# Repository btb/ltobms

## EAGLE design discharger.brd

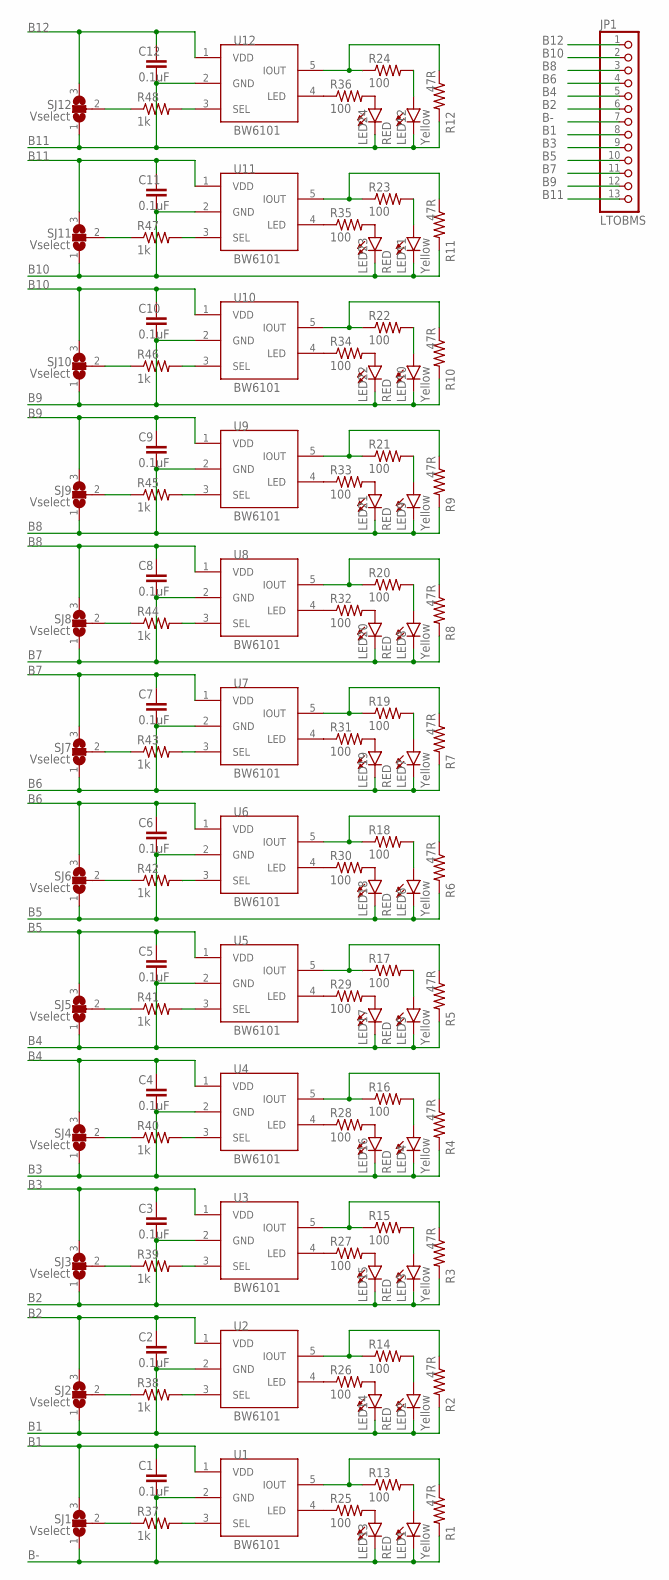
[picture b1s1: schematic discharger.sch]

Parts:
C1, C2, C3, C4, C5, C6, C7, C8, C9, C10, C11, C12: 0.1uF; C0603; LCSCPART# C49678
JP1: LTOBMS; 1X13
LED1, LED2, LED3, LED4, LED5, LED6, LED7, LED8, LED9, LED10, LED11, LED12: Yellow; LED-0603; LCSCPART# C84256
LED13, LED14, LED15, LED16, LED17, LED18, LED19, LED20, LED21, LED22, LED23, LED24: RED; LED-0603; LCSCPART# C84256
R1, R2, R3, R4, R5, R6, R7, R8, R9, R10, R11, R12: 47R; R2512; LCSCPART# C25384
R13, R14, R15, R16, R17, R18, R19, R20, R21, R22, R23, R24, R25, R26, R27, R28, R29, R30, R31, R32, R33, R34, R35, R36: 100; R0603; LCSCPART# C17408
R37, R38, R39, R40, R41, R42, R43, R44, R45, R46, R47, R48: 1k; R0603; LCSCPART# C17513
SJ1, SJ2, SJ3, SJ4, SJ5, SJ6, SJ7, SJ8, SJ9, SJ10, SJ11, SJ12: Vselect; SJ_2
U1, U2, U3, U4, U5, U6, U7, U8, U9, U10, U11, U12: BW6101; SOT23-5L

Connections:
B1: C1.1, C2.2, JP1.8, LED2.C, LED14.C, R2.2, SJ1.3, SJ2.1, U1.1 (VDD), U2.2 (GND)
B2: C2.1, C3.2, JP1.6, LED3.C, LED15.C, R3.2, SJ2.3, SJ3.1, U2.1 (VDD), U3.2 (GND)
B3: C3.1, C4.2, JP1.9, LED4.C, LED16.C, R4.2, SJ3.3, SJ4.1, U3.1 (VDD), U4.2 (GND)
B4: C4.1, C5.2, JP1.5, LED5.C, LED17.C, R5.2, SJ4.3, SJ5.1, U4.1 (VDD), U5.2 (GND)
B5: C5.1, C6.2, JP1.10, LED6.C, LED18.C, R6.2, SJ5.3, SJ6.1, U5.1 (VDD), U6.2 (GND)
B6: C6.1, C7.2, JP1.4, LED7.C, LED19.C, R7.2, SJ6.3, SJ7.1, U6.1 (VDD), U7.2 (GND)
B7: C7.1, C8.2, JP1.11, LED8.C, LED20.C, R8.2, SJ7.3, SJ8.1, U7.1 (VDD), U8.2 (GND)
B8: C8.1, C9.2, JP1.3, LED9.C, LED21.C, R9.2, SJ8.3, SJ9.1, U8.1 (VDD), U9.2 (GND)
B9: C9.1, C10.2, JP1.12, LED10.C, LED22.C, R10.2, SJ9.3, SJ10.1, U9.1 (VDD), U10.2 (GND)
B10: C10.1, C11.2, JP1.2, LED11.C, LED23.C, R11.2, SJ10.3, SJ11.1, U10.1 (VDD), U11.2 (GND)
B11: C11.1, C12.2, JP1.13, LED12.C, LED24.C, R12.2, SJ11.3, SJ12.1, U11.1 (VDD), U12.2 (GND)
B12: C12.1, JP1.1, SJ12.3, U12.1 (VDD)
B-: C1.2, JP1.7, LED1.C, LED13.C, R1.2, SJ1.1, U1.2 (GND)
unnamed: R1.1, R13.1, U1.5 (IOUT)
unnamed: LED1.A, R13.2
unnamed: R25.1, U1.4 (LED)
unnamed: LED2.A, R14.2
unnamed: LED7.A, R19.2
unnamed: R3.1, R15.1, U3.5 (IOUT)
unnamed: R37.1, SJ1.2
unnamed: R38.1, SJ2.2
unnamed: R27.1, U3.4 (LED)
unnamed: LED15.A, R27.2
unnamed: LED8.A, R20.2
unnamed: R39.1, SJ3.2
unnamed: R40.1, SJ4.2
unnamed: LED9.A, R21.2
unnamed: LED13.A, R25.2
unnamed: R8.1, R20.1, U8.5 (IOUT)
unnamed: R41.1, SJ5.2
unnamed: R42.1, SJ6.2
unnamed: R32.1, U8.4 (LED)
unnamed: LED20.A, R32.2
unnamed: R2.1, R14.1, U2.5 (IOUT)
unnamed: R43.1, SJ7.2
unnamed: R44.1, SJ8.2
unnamed: R26.1, U2.4 (LED)
unnamed: LED14.A, R26.2
unnamed: R4.1, R16.1, U4.5 (IOUT)
unnamed: R45.1, SJ9.2
unnamed: R46.1, SJ10.2
unnamed: R28.1, U4.4 (LED)
unnamed: LED16.A, R28.2
unnamed: LED10.A, R22.2
unnamed: LED11.A, R23.2
unnamed: LED12.A, R24.2
unnamed: LED6.A, R18.2
unnamed: LED5.A, R17.2
unnamed: R5.1, R17.1, U5.5 (IOUT)
unnamed: R47.1, SJ11.2
unnamed: R48.1, SJ12.2
unnamed: R29.1, U5.4 (LED)
unnamed: LED17.A, R29.2
unnamed: R9.1, R21.1, U9.5 (IOUT)
unnamed: R48.2, U12.3 (SEL)
unnamed: R47.2, U11.3 (SEL)
unnamed: R33.1, U9.4 (LED)
unnamed: LED21.A, R33.2
unnamed: R6.1, R18.1, U6.5 (IOUT)
unnamed: R46.2, U10.3 (SEL)
unnamed: R45.2, U9.3 (SEL)
unnamed: R30.1, U6.4 (LED)
unnamed: LED18.A, R30.2
unnamed: LED4.A, R16.2
unnamed: LED3.A, R15.2
unnamed: R44.2, U8.3 (SEL)
unnamed: R43.2, U7.3 (SEL)
unnamed: R42.2, U6.3 (SEL)
unnamed: R7.1, R19.1, U7.5 (IOUT)
unnamed: R41.2, U5.3 (SEL)
unnamed: R40.2, U4.3 (SEL)
unnamed: R31.1, U7.4 (LED)
unnamed: LED19.A, R31.2
unnamed: R10.1, R22.1, U10.5 (IOUT)
unnamed: R39.2, U3.3 (SEL)
unnamed: R38.2, U2.3 (SEL)
unnamed: R34.1, U10.4 (LED)
unnamed: LED22.A, R34.2
unnamed: R37.2, U1.3 (SEL)
unnamed: R11.1, R23.1, U11.5 (IOUT)
unnamed: R35.1, U11.4 (LED)
unnamed: LED23.A, R35.2
unnamed: R12.1, R24.1, U12.5 (IOUT)
unnamed: R36.1, U12.4 (LED)
unnamed: LED24.A, R36.2

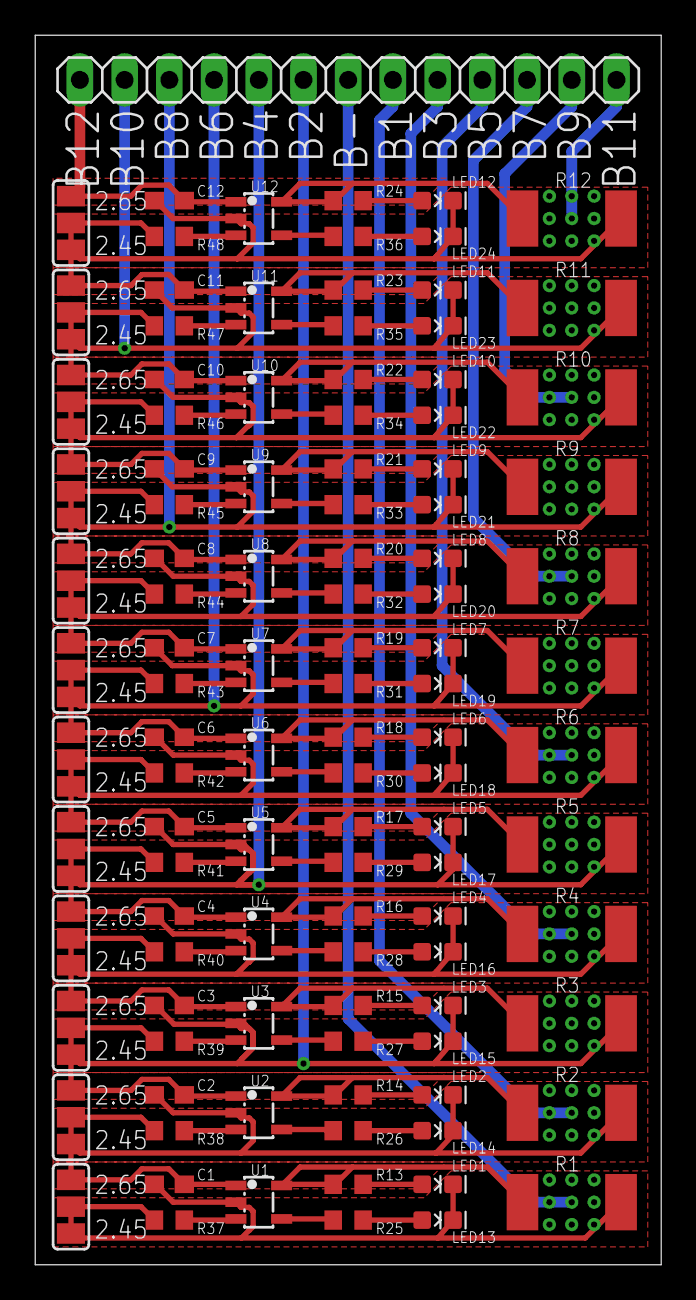
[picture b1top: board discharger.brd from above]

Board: 2 copper layers, 35.6 x 69.8 mm, 109 parts (0 on the bottom side), 85 nets.

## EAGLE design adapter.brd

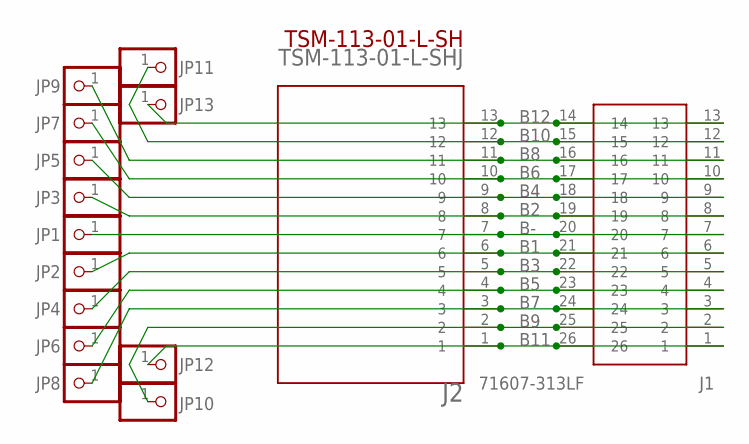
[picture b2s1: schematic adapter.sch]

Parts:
J1: 71607-313LF; 71607313LF
J2: TSM-113-01-L-SHJ; TSM-113-01-L-SH
JP1, JP2, JP3, JP4, JP5, JP6, JP7, JP8, JP9, JP10, JP11, JP12, JP13: PINHD-1X1; 1X01BIG

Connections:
B1: J1.6, J1.21, J2.6, JP2.1
B2: J1.8, J1.19, J2.8, JP3.1
B3: J1.5, J1.22, J2.5, JP4.1
B4: J1.9, J1.18, J2.9, JP5.1
B5: J1.4, J1.23, J2.4, JP6.1
B6: J1.10, J1.17, J2.10, JP7.1
B7: J1.3, J1.24, J2.3, JP8.1
B8: J1.11, J1.16, J2.11, JP9.1
B9: J1.2, J1.25, J2.2, JP10.1
B10: J1.12, J1.15, J2.12, JP11.1
B11: J1.1, J1.26, J2.1, JP12.1
B12: J1.13, J1.14, J2.13, JP13.1
B-: J1.7, J1.20, J2.7, JP1.1

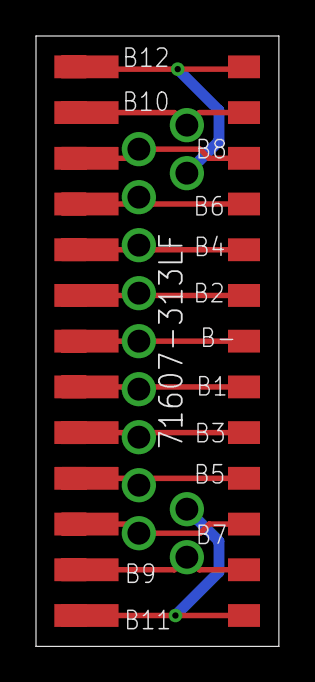
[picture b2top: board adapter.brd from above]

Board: 2 copper layers, 13.5 x 33.9 mm, 15 parts (0 on the bottom side), 13 nets.

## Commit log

2020-08-10 add BMS to SIL adapter board
2020-08-10 add description
2020-08-10 add part library
2020-08-11 add schematic
2020-08-12 make a single cell protector as a design block
2020-08-12 don't use pwr for the BW6101 ground pin
2020-08-12 use the design block
2020-08-12 add the board
2020-08-12 fix layer
2020-08-12 ignore design block backup files
2020-08-12 add url and revision
2020-08-12 move url
2020-08-12 make pdf
2020-08-12 add .1uF capacitor to chip
    use some 0603 parts, better layout
2020-08-12 more layout, update pdf
2020-08-12 layout tweaks
2020-08-12 tweaks
2020-08-12 add CAM outputs
2020-08-13 use 2512 resistors to dissipate more power
2020-08-13 update CAMOutputs
2020-08-13 bump version, minor changes
2020-08-16 move 1k resistor onto SEL side of jumper
    more fiddling
2020-08-17 update CAM
2020-08-19 add orientation dot
2020-08-19 custom parts for LEDs, misc fixes
2020-08-20 update gerbers
2020-08-20 include drill file
2020-08-20 add gerbers for adapter
2020-09-08 update adapter board for SMD
2020-09-08 add cam config file
2020-09-08 add labels
2020-09-08 make part name visible
2020-09-08 minimize pcb size
2020-09-08 fix labels
2020-09-08 regenerate
2020-09-09 add samtec footprint for more compatibility
2020-09-09 fix dimension wires
2020-09-10 adjust labels, add traces to pre-set 2.45V
2020-09-10 board revision 0.04
2020-09-10 text tweak
